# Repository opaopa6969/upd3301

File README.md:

**日本語** · [English](./README.en.md)

# upd3301 — NEC μPD3301 CRTコントローラ エミュレータ

NEC PC-8001（1979）の画面に文字を出していた張本人、μPD3301 CRTC と、その
相棒 μPD8257 DMAコントローラのチップレベル・エミュレータ。pure JavaScript・
依存ゼロ・決定論・headlessテスト可能。

## なんで作ったか（3301記念）

偶然の連鎖の記念碑として作った：アニメ『ヤニねこ』OPの「3301！3301！」→
実はサイゼリヤの生ビールの注文番号 → そして僕らが一番懐かしい3301、
μPD3301 へ。すべては3301に帰る。

## 使い方 — いちばん簡単な始め方

著作権上、NEC の ROM やゲームは同梱していません（自分の実機吸い出しを使ってください）。[PC-8801 デモ](./demo/machine.html)を開いて:

1. **💽ディスク → 📚一覧 → 📁フォルダを開く** で、**ROM や D88 の入ったフォルダを雑に指定するだけ**（例 `C:\\var\\emulator`）
2. フォルダを再帰スキャンして **PC-8801 BIOS一式・font・数百本のゲーム**を全部見つけ、検索付き一覧に並べる（一度許可すれば次回も記憶）
3. 一覧からゲームをクリック → 起動。進行は自動セーブされ、次回は「▶ 前回の続きから再開」

ファイルは**あなたの端末に残ったまま**（ハンドルだけ保持。著作物をどこにもアップしない設計）。フォルダ選択は Chrome 系ブラウザで動作（File System Access API）。個別に「📁ファイル選択」で ROM/ディスクを選ぶ従来方式も可。

## ブラウザだけで、遊ぶ・作る・改造する

- **ジョグシャトル**プレイヤー（ビデオデッキ風。巻き戻し／早送り、現在を追い越すと実エミュを×16で爆走、非破壊シークで未来へ、10分バッファ）
- **セッション自動セーブ＆再開**（うっかりリセットやタブを閉じても続きから）
- **ICE / IDE デバッガ**（条件ブレーク・時間旅行・プロファイラ・Z80マクロアセンブラ・逆アセン。パネルは tmux 式に列で自由配置＋別ウィンドウ切り離し）
- **サウンドボードII (OPNA)**、**CRTシミュレーション**（残光・高精細アパーチャ/シャドウマスク・走査線・アナログ色）、**WebM録画**
- ROM・ディスク・設定・進行はブラウザ(IndexedDB)に保存。閉じても残る。データはどこにも送信しない。

## エミュレートしてるもの

- **μPD3301 コア**（`index.js`）: コマンド/ステータスポート（PC-8001の
  I/O 51h）、パラメータポート（50h）、RESETの5バイトパラメータ（桁数・
  行数・文字あたりライン数・ブリンク周期・カーソルモード・水平/垂直
  ブランキング・アトリビュート数とモード）、反転ビット付きSTART DISPLAY、
  割り込みマスク、カーソル設定、1行 `文字数 + 2×アトリビュート数` バイトの
  行DMA、fill-forward方式のアトリビュート展開、DMAアンダーラン、VRTC
  フレーム終端割り込み、決定論的なカーソル/アトリビュートブリンク。
- **μPD8257 モデル**（`upd8257.js`）: 4チャネル、上位/下位バイトの
  フリップフロップ、readモードのターミナルカウント、TCステータス、
  オートロード（ch2がch3から再装填 — PC-8001が毎フレーム同じ画面を
  繰り返す仕組み）。
- **PC-8001 配線**（`pc8001.js`）: 64KBメモリ + DMAC ch2 + CRTC を実機の
  ポートマップ（30h/50h/51h/60h〜68h）で接続。テキストVRAMは F3C8h、
  1行120バイト（80文字 + アトリビュート20ペア）。カラー指定
  （bit3=1: GRB+セミグラ）と機能指定（bit3=0: 反転・点滅・シークレット・
  上下線・白黒セミグラ）の2状態デコード、2×4ブロックのセミグラフィック、
  40/80桁のドット倍幅、CGROM注入式のインデックスカラーレンダラ
  （著作権フォントは同梱しない）。

チップコアは自分でメモリを触らない。DRQを上げてDMAモデルにバイトを
食わせてもらう — 実機のバスと同じ。だからベーマガ1990年7月号の
「MAGICAL COLOR」がそのまま動く：DMAカウントを2フレーム分
（port 65h ← 8000h + 5999）にすると2画面が毎フレーム交互に出て、
ちらつき混色で8色が27色になる。テストもある。さらに**3フレーム分**に
するとRGBプレーンモード：論理的にはドット単位フルカラー、ただし各ガンの
デューティは1/3で暗い。それが見えるかは残光次第 — というわけで物理層がある：

- **蛍光体物理**（`crt.js`）: ガンごとの2成分減衰（速い閃光＋遅い燐光。
  双曲的減衰の近似）、差動残光（P22は青が先に死ぬので白の残像はオレンジに
  変色して消える）、発光色（P39は何を映しても緑。P7レーダー管は青白い
  閃光→黄緑の残光）、焼き付き（累積ドーズで効率低下）、インターレース励起
  （フィールドごとのライン偶奇）。
- **管物理**（`tube.js`）: シャドウマスク/アパーチャグリル/スロットマスクの
  透過パターン＋ガウシアンビームスポットの前段ブラー（**滲みはマスクから
  生まれる**）、曲面ガラスのバレル歪み、ガラス内面反射の薄いゴースト、
  コーナーのビネット。全部LUTに事前計算、決定論。
- **音鳴り**: `crtc.hsyncHz()` が設定ジオメトリから水平偏向周波数を導出 —
  (25+7行)×8ライン×60Hz = **15360Hz**。デモで鳴らせる。あの音だよ。
- **ターミナル層**（`term.js`）: まともな書き込みインターフェイス —
  カーソル/スクロール付き `write()`、ANSIエスケープシーケンス（SGRの
  色・反転・点滅・下線、カーソル移動、消去）を `flush()` でチップの
  （位置, 値）アトリビュートペアにコンパイル。N-BASICの SET/RESET 感覚の
  セミグラAPI（`setDot`/`resetDot`/`dot`）付き。実機制約モード（80×25・
  20ペア/行 → 溢れたら `stats.overflowRows` に計上）と **EXモード**
  （`resetEx`/`setChannelEx` の架空シリコン改版。任意の桁×行＋セル単位
  アトリビュート）の両対応 — ターミナルとして使える。`demo/terminal.html`。

- **フルマシン**（`machine.js`＋`demo/machine.html`）: Z80＋手持ちの
  N-BASIC ROM吸い出し＋上記チップ群＝起動するPC-8001。
  `node tools/boot-nbasic.mjs roms/N80.ROM` で起動画面をダンプ、
  統合テストはキーボードマトリクス経由で `PRINT 3301` を打って答えを
  検証する。ROMはBYO（gitignore済み）— NECの著作権は2049年まで。

ICE設計 — デバッガ・時間旅行・アセンブラ・リバース用「石器一式」
（ラベル・ソース書き出し・検証付きリロケート）:
[docs/ice-design.ja.md](./docs/ice-design.ja.md)。

解析成果の共有形式（`analysisdb.js` / `analysis/<machine>/<slug>.json`）— ラベル・乱数
マップ・調査記録を、**confidence と evidence と romHash つき**で PR として共有する。
衝突は黙って上書きせず conflicts に残す:
[docs/analysis-format.ja.md](./docs/analysis-format.ja.md)。

各部品をライブラリとして使う（CRTレンダラー・ターミナル・マシン）:
[docs/library.ja.md](./docs/library.ja.md)。

他エミュ（QUASI88 / MAME / M88）とのソースレベル比較 — MAMEとM88も同じく
チップレベルだった。うちが唯一持つのはその下の物理層:
[docs/comparison.ja.md](./docs/comparison.ja.md)。

チップレベルの技術資料（データシート風、mermaidブロック図つき）:
[docs/datasheet.ja.md](./docs/datasheet.ja.md)。

第2巻 — 周辺チップ編（8255 / μPD765 / μPD8214 / 8251 / クロック体系）: [docs/peripherals.ja.md](./docs/peripherals.ja.md)。

## 使い方

```js
import { Pc8001TextSystem } from './pc8001.js';

const sys = new Pc8001TextSystem();
sys.initTextMode();                     // N-BASIC起動と同じ手順でCRTC+DMACを設定
sys.line(0).text(0, 'HELLO 3301').attrs(0, 0xe8);
sys.update(1 / 60);                     // 固定ステップ・フレーム正確
const { width, height, pixels } = sys.render({ cgrom }); // 0..7 の色インデックス
```

素のチップをポート経由で叩くなら `crtc.writePort(1, 0x00)` …
完全なシーケンスは `test.mjs` を見て。

```sh
node --test              # 決定論テスト一式（要 node>=24）
python3 -m http.server   # リポジトリ直下で実行 → http://localhost:8000/demo/ を開く
```

デモは全レイヤにボタンがある：テキスト/27色/RGB3プレーン、40/80桁、
画面反転、蛍光体4種、焼き付き、マスク3種、インターレース、15kHz音鳴り
（ブラウザの自動再生制限があるのでクリックで開始）。

## 正確性メモ

忠実：コマンド体系、RESETパラメータのデコード、行DMAのバイト数、
アトリビュート展開の意味論（fill-forward、2ペイア以降の位置0=行末）、
アンダーランで落ちる非公開bit7を含むステータス、8257オートロード。
近似：タイミングはフレーム粒度（ドットクロックなし、フレーム途中の
VRTC観測不可）、ライトペンと特殊制御文字は未対応、ブリンク周期は
資料の式どおりだが実チップ未検証。ブラウザデモの実描画はheadlessでは
見られないため visual未検証（smoke testのみ）。

## MCP

namespace `upd3301` — Z80アセンブラ/逆アセンブラ, CRT物理レンダラー,
ROM識別, 解析DB検証/マージ, D88ディスク読み取りを MCP tool として公開。
能力仕様は `upd3301://spec` resource、使い方は `upd3301://guide`。
volta ファサード `https://mcp.unlaxer.org/mcp` 経由で `upd3301__*` で呼べる。
起動: `PORT=9270 node mcp/server.mjs`（`/healthz` + `/mcp`, 0.0.0.0 bind）。
詳細は [docs/mcp/DESIGN.md](docs/mcp/DESIGN.md)。

## 参考資料

- MAME `src/devices/video/upd3301.cpp`（挙動の参照。コードはコピーせず再実装）
- [nkomatsuさんのICコレクション: uPD3301](http://www.st.rim.or.jp/~nkomatsu/crtif/uPD3301.html)
- [kwhr0さんのPC-8001 FPGAノート](http://kwhr0.g2.xrea.com/hard/pc8001.html)（1行120バイトのバッファ、水平帰線中DMA）
- [EnrPc PC-8001ポートマップ](http://cmpslv3.stars.ne.jp/Pc80/EnrPc.htm)
- [PC-8001で27色](http://wwwb.pikara.ne.jp/minosoft/pc-8001/color.htm)（ベーマガ1990年7月号「MAGICAL COLOR」）

MITライセンス。NECとは無関係の趣味プロジェクト。

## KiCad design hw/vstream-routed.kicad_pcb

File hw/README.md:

**English** · [日本語](./README.ja.md)

# VSTREAM — feeding 2026 video into a 1979 PC-8001

An expansion-bus adapter that streams `.p8v` frame data (this repo's
converted video) from a microSD card into a real PC-8001, so the actual
μPD3301 displays it. The 1979 bottleneck was never compute or display — it
was storage bandwidth (a 92s clip = 8.3MB = 58 floppies). This board is
that missing 47-year bridge.

## Architecture

```mermaid
flowchart LR
  SD[microSD<br/>.p8v frames] --SPI--> PICO[RP2040 Pico<br/>core0: SD read<br/>PIO: bus slave]
  PICO --8bit--> LVC1[74LVC245<br/>data driver]
  LVC1 --> BUS[PC-8001<br/>expansion bus]
  BUS --A1-A7,/M1--> CMP[74HC688<br/>= port 70h?]
  CMP --> OR[74HC32<br/>+/IORQ +/RD +A0]
  OR --/OE--> LVC1
  OR --sense--> LVC2[74LVC245<br/>5V→3.3V] --> PICO
  PICO --gate--> FET[2N7002] --/WAIT--> BUS
```

- **One read-only I/O port (70h)** — the Z80 player just runs `INIR`.
- **Hardware flow control via /WAIT**: if the Pico's FIFO is empty the IN
  cycle stretches until data is ready. No status port, no polling.
- **Level shifting**: 74LVC245 (5V-tolerant inputs, 3.3V outputs satisfy
  TTL V_IH=2.0V) — the standard retro-interfacing recipe.
- Address decode: 74HC688 compares A1–A7 + /M1 (interrupt-ack excluded),
  qualified with /IORQ, /RD, A0 through 74HC32 → `/OE`.

## Z80 player (15 fps, double-buffered via DMA flip)

```asm
PORT    equ 70h
PAGE0   equ 0C000h          ; two 3000-byte VRAM pages
PAGE1   equ 0CC00h
        ; ... CRTC/DMAC init as in the demo (see test-z80.mjs) ...
frame:  ld   hl, backpage    ; fill the page the DMA is NOT reading
        ld   d, 12           ; 12 x 250 = 3000 bytes
chunk:  ld   b, 250
        ld   c, PORT
        inir                 ; /WAIT paces us — no status polling
        dec  d
        jr   nz, chunk
        call flipdma         ; OUT 64h/65h: point ch2/ch3 at the new page
        jr   frame
```

Budget: `INIR` = 21 T-states/byte × 3000 = 63k T + overhead, ~16 frames/s
on a 4 MHz Z80 **before** the ~30% DMA display steal → target 15 fps with
frames duplicated at authoring time. `.p8v` format: `"P8V1"`, u8 cols, u8
rows, u8 fps, then frames of `rows × (cols + 40)` bytes.

## Files

- `vstream_netlist.py` — skidl source (run with python3.10)
- `vstream.net` — **ERC-checked KiCad netlist** (0 errors)
- `bom.csv` — bill of materials

## To fab — ALREADY DONE (headless pipeline)

This repo now contains the full chain, executed without opening a GUI:

1. `vstream_netlist.py` (skidl, ERC 0 errors) → `vstream.net`
2. `make_pcb.py` (pcbnew 6 python) → placed board + custom Pico footprint
   (`vstream.pretty/`) + board outline → `vstream.kicad_pcb` + Specctra DSN
3. freerouting 1.9 headless → `vstream.ses` (routed in 4.5 s, optimizer +50%)
4. `ses_import.py` — parses the SES s-expressions and injects 423 track
   segments + 17 vias (KiCad 6 standalone can't ImportSpecctraSES, so we
   became the importer) → `vstream-routed.kicad_pcb`,
   **connectivity check: 0 unconnected**
5. Gerber + Excellon drill → **`vstream-gerber.zip`** — a board house
   would accept this file today

**Do not actually order it yet**: J1's pin numbering is still a
placeholder. Verify against the PC-8001 service manual, re-run steps 1-5
(one command each), then order.

## Honesty section

ERC-verified netlist; **not silicon-verified**. J1 (expansion connector)
pin numbers are placeholders — verify against the PC-8001 service manual
before layout. The RP2040 PIO program and the SD reader firmware are not
written yet (issue #3). Timing margins (LVC245 ~5ns prop, preloaded data)
should give zero wait states when the FIFO is full, but nobody has scoped
it. This is a design study you could hand to a fab — after one afternoon
of pinout verification.

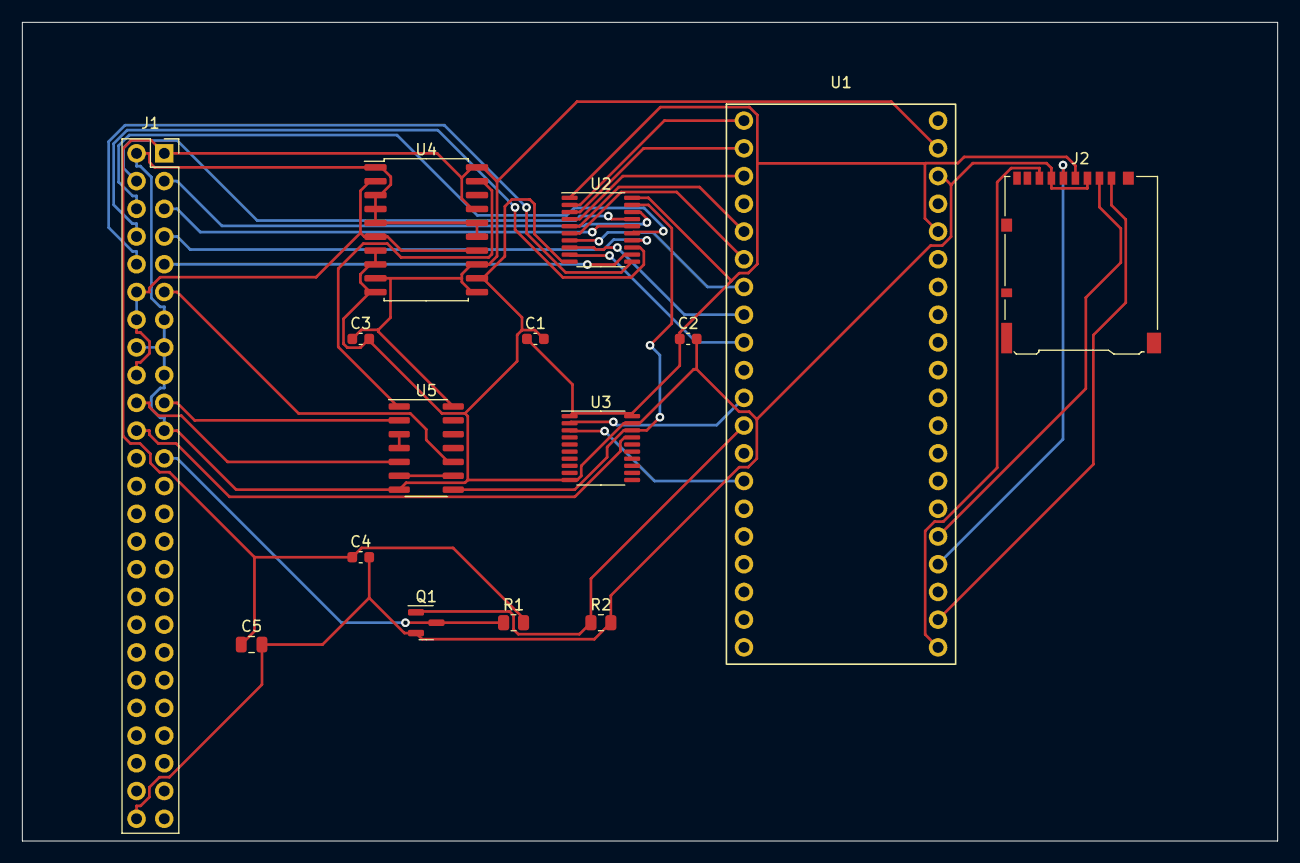
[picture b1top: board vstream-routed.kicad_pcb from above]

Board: 2 copper layers, 115.0 x 75.0 mm, 15 parts (0 on the bottom side), 36 nets.

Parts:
C1, C2, C3, C4: C_100n; C_0603_1608Metric
C5: C_10u; C_0805_2012Metric
J1: PC8001_EXPANSION; PinSocket_2x25_P2.54mm_Vertical
J2: microSD_SPI; microSD_HC_Hirose_DM3AT-SF-PEJM5
Q1: 2N7002; SOT-23
R1: R_4k7; R_0805_2012Metric
R2: R_10k; R_0805_2012Metric
U1: RPi_Pico; RPi_Pico_TH
U2, U3: 74LVC245A; TSSOP-20_4.4x6.5mm_P0.65mm
U4: 74HC688; SOIC-20W_7.5x12.8mm_P1.27mm
U5: 74HC32; SOIC-14_3.9x8.7mm_P1.27mm

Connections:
+3V3: C1.1, C2.1, J2.4, U1.36, U2.1, U2.20, U3.1, U3.20
+5V: C3.1, C4.1, C5.1, J1.1, R1.2, U1.39, U4.9, U4.11, U4.13, U4.17, U4.20, U5.14
A0: J1.11, U5.10
A2: C1.2, C2.2, C3.2, C4.2, C5.2, J1.2, J1.13, J1.15, J1.16, J1.17, J1.21, J1.50, J2.3, J2.6, Q1.2, R2.2, U1.38, U2.10, U3.10, U3.19, U4.1, U4.3, U4.4, U4.5, U4.7, U4.8, U4.10, U4.12, U4.15, U4.16, U5.7
A3: J1.12, J1.14, J1.18, U4.2, U4.6, U4.14
D0: J1.3, U2.18
D1: J1.4, U2.17
D2: J1.5, U2.16
D3: J1.6, U2.15
D4: J1.7, U2.14
D5: J1.8, U2.13
D6: J1.9, U2.12
D7: J1.10, U2.11
OE33: U1.11, U3.2
OR1: U5.3, U5.4
OR2: U5.6, U5.9
PD0: U1.1, U2.2
PD1: U1.2, U2.3
PD2: U1.3, U2.4
PD3: U1.5, U2.5
PD4: U1.6, U2.6
PD5: U1.7, U2.7
PD6: U1.8, U2.8
PD7: U1.9, U2.9
RST33: U1.14, U3.3
SD_CS: J2.1, U1.22
SD_MISO: J2.7, U1.21
SD_MOSI: J2.2, U1.25
SD_SCK: J2.5, U1.24
WAIT_GATE: Q1.1, R2.1, U1.12
~IORQ: J1.19, U5.2
~OE_READ: U2.19, U3.18, U5.8
~RD: J1.20, U5.5
~RESET: J1.22, U3.17
~SEL: U4.19, U5.1
~WAIT: J1.23, Q1.3, R1.1

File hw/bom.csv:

Ref,Part,Package,Qty,Note
U1,Raspberry Pi Pico,module (2x20 header),1,RP2040: PIO bus IF + SD read
U2,74LVC245A,TSSOP-20,1,"data driver Pico->bus (5V-tol in, 3.3V out = TTL VIH ok)"
U3,74LVC245A,TSSOP-20,1,control sense 5V->3.3V
U4,74HC688,SOIC-20W,1,address compare: port 70h + /M1 qualify
U5,74HC32,SOIC-14,1,/OE = /SEL|/IORQ|/RD|A0
Q1,2N7002,SOT-23,1,/WAIT open-drain (hardware flow control)
R1,4.7k,0805,1,/WAIT pull-up to +5V
R2,10k,0805,1,WAIT gate pull-down (release on boot)
C1-C4,100nF,0603,4,decoupling
C5,10uF,0805,1,bulk
J1,PC-8001 expansion,2x25 2.54mm (verify!),1,PINOUT PLACEHOLDER - check service manual
J2,microSD,Hirose DM3AT,1,SPI mode
